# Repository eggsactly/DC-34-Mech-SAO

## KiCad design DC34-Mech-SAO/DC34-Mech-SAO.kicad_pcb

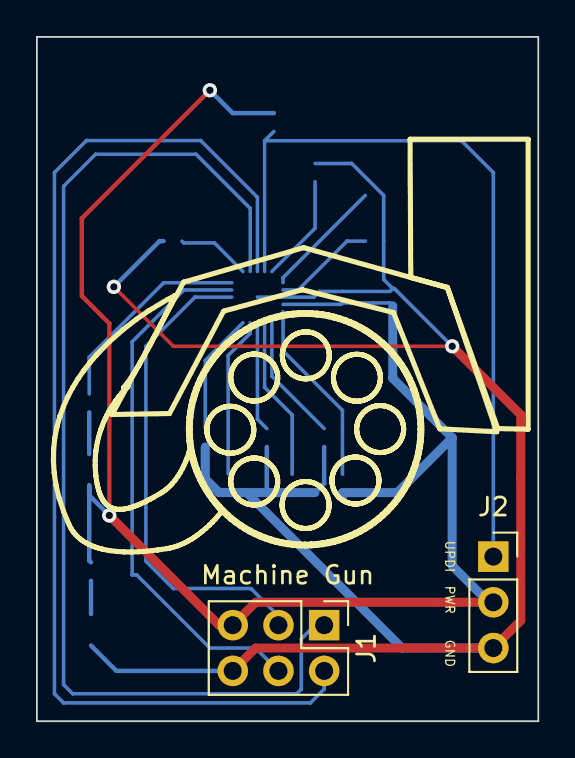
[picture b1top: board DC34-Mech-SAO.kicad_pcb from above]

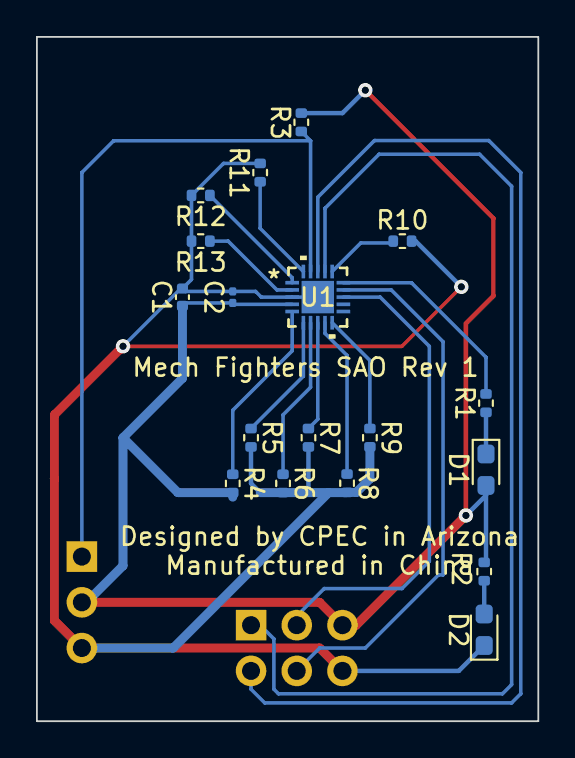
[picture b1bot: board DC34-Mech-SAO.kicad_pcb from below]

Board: 2 copper layers, 27.9 x 38.0 mm, 20 parts (18 on the bottom side), 20 nets.

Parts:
C1: 10uF; C_0402_1005Metric
C2: 0.1uF; C_0201_0603Metric
D1: GREEN; LED_0603_1608Metric_Pad1.05x0.95mm_HandSolder
D2: RED; LED_0603_1608Metric_Pad1.05x0.95mm_HandSolder
J1: Conn_01x06_Male; PinHeader_2x03_P2.54mm_Vertical
J2: Conn_01x03_Male; PinSocket_1x03_P2.54mm_Vertical
R1, R2, R3, R4, R5, R6, R7, R8, R9, R10, R11, R12, R13: 10k; R_0402_1005Metric
U1: ATtiny816-M; VQFN20_3X3_MCH

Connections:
GND: C1.2, C2.2, D2.1 (K), J1.6, J2.3, R5.2, R6.2, R7.2, R8.2, R9.2, R10.2, R11.2, R12.2, R13.2, U1.3 (GND), U1.21 (GND)
GPIO1: J1.1, U1.17 (PC2)
GPIO2: J1.2, U1.18 (PC3)
IO0: R4.1, U1.5 (PA4)
IO1: R5.1, U1.6 (PA5)
IO2: R6.1, U1.7 (PA6)
IO3: R7.1, U1.8 (PA7)
IO4: R8.1, U1.9 (PB5)
IO5: R9.1, U1.10 (PB4)
IO6: R10.1, U1.16 (PC1)
IO7: R11.1, U1.20 (PA1)
IO8: R12.1, U1.1 (PA2)
IO9: R13.1, U1.2 (PA3)
unnamed: D1.1 (K), R1.1
unnamed: D2.2 (A), R2.2
unnamed: R1.2, U1.15 (PC0)
PWR: C1.1, C2.1, D1.2 (A), J1.5, J2.2, R2.1, R3.2, R4.2, U1.4 (VCC)
SCL: J1.4, U1.14 (PB0)
SDA: J1.3, U1.13 (PB1)
UPDI: J2.1, R3.1, U1.19 (~RESET/PA0)

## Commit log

2026-04-14 Initial commit.
2026-04-27 Updated .gitignore to ignore .png files.
2026-04-27 Removed space from weapons draft.
2026-04-27 change 1
    added missile launcher
2026-04-27 change_3
    added laser cannon
2026-05-01 Updated Traces for Design Rule Check
    Made it so that power and ground traces do not violate design rule checks.
2026-05-02 Removed zip files.
2026-05-02 Added silkscreen
    Added descriptive text to board.
